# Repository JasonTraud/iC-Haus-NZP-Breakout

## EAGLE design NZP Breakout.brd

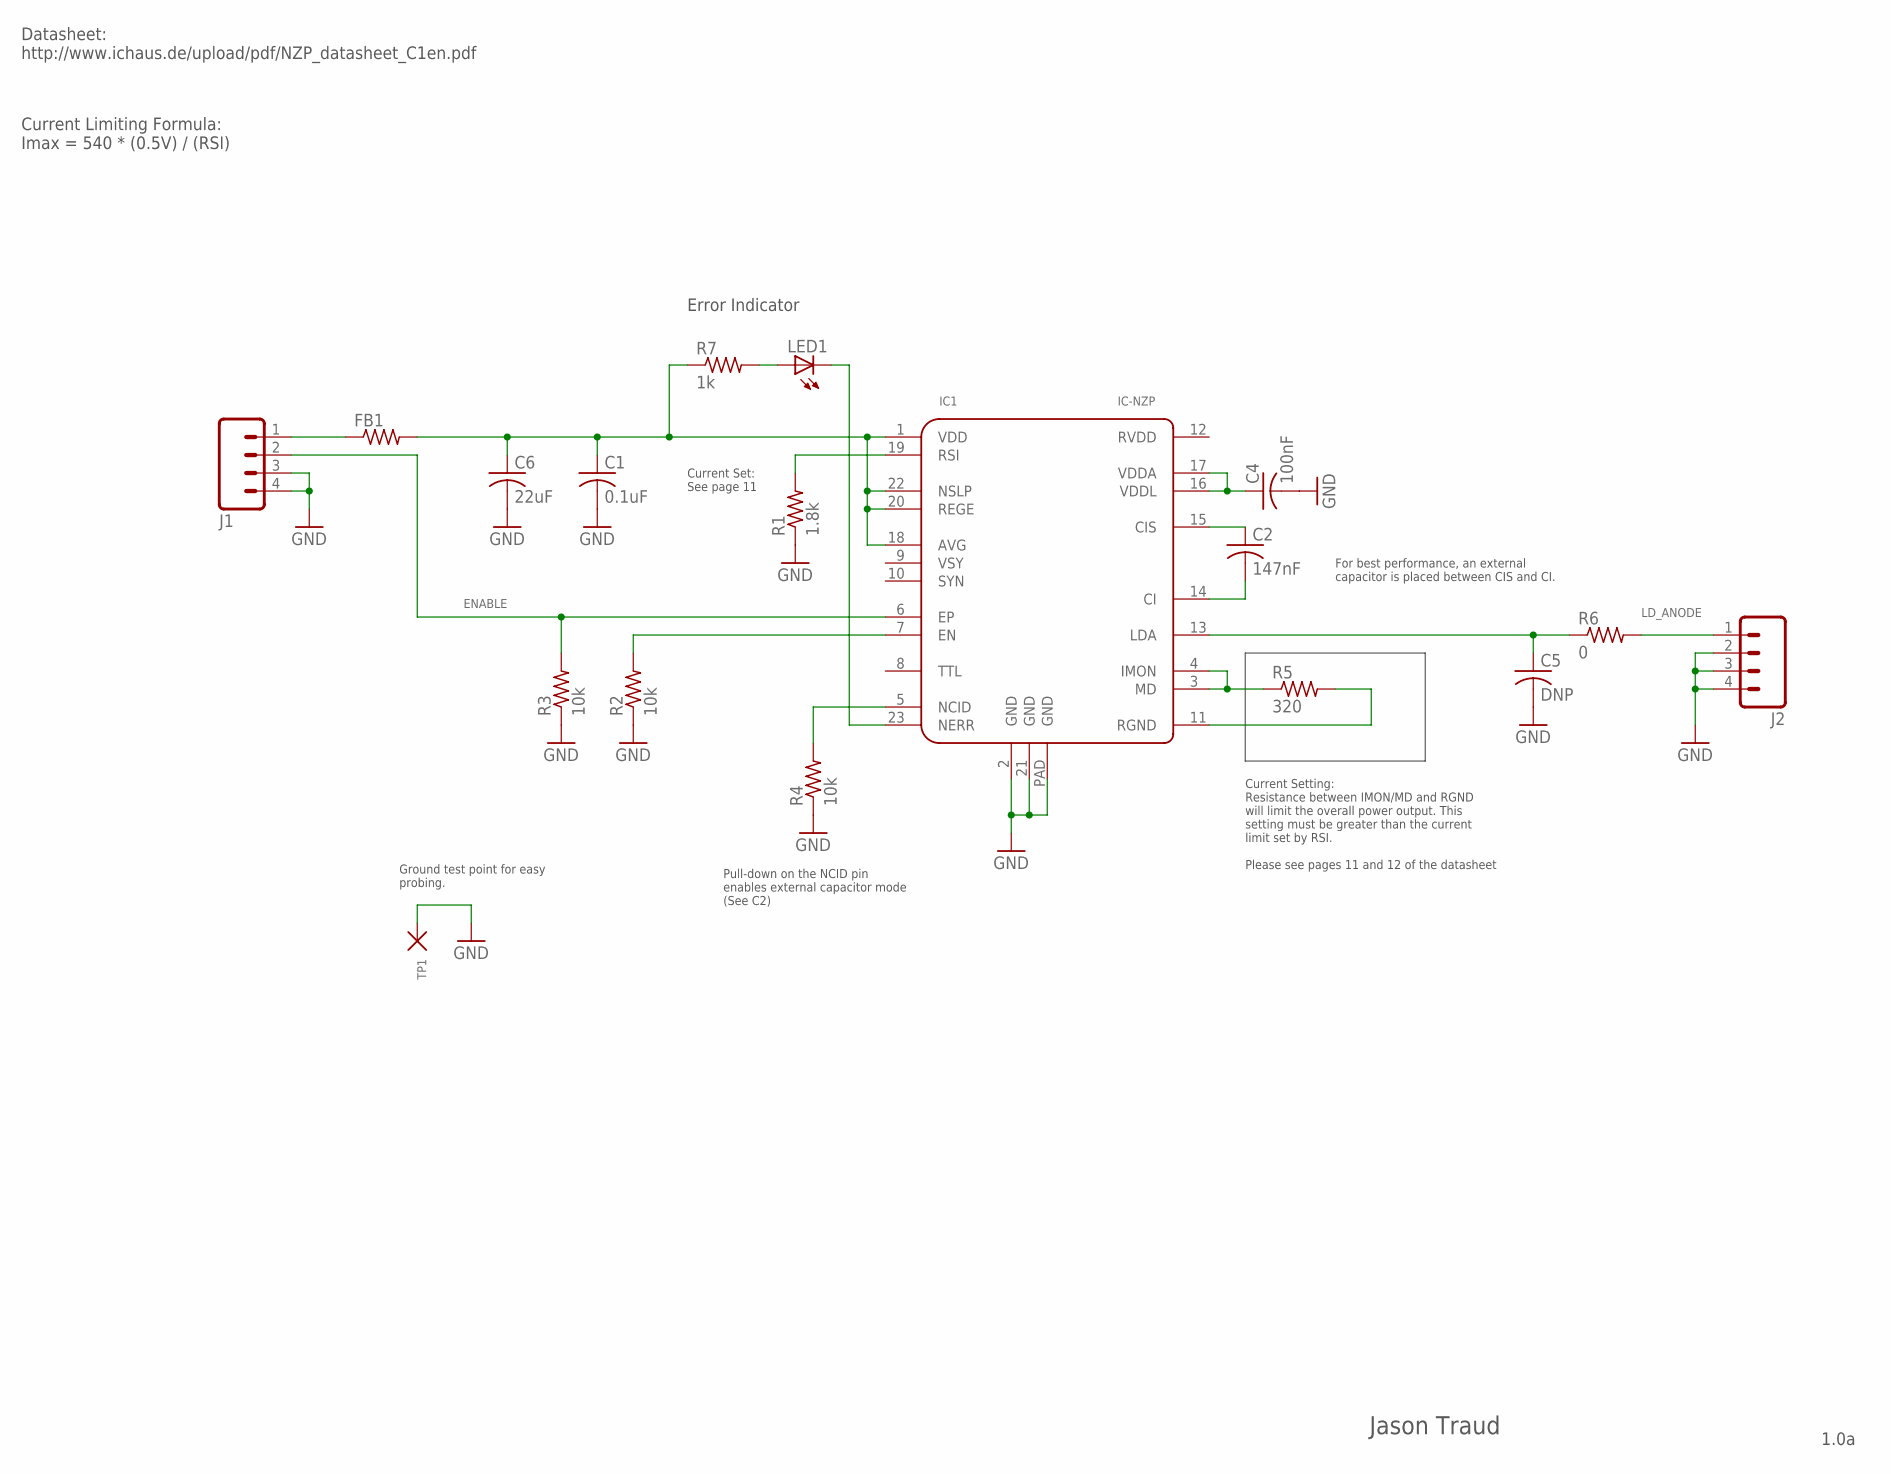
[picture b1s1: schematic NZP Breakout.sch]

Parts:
C1: 0.1uF; C0402
C2: 147nF; C0402
C4: 100nF; C0402
C5: DNP; C0805
C6: 22uF; C1206; MFG_PN TCTAL1C226M8R
FB1: R-US_R0805; R0805; MFG_PN MPZ2012S300A
IC1: IC-NZP; QFN24_PAD
J1, J2: 2X2; 2X2_1.27MM
LED1: LEDSML0805; SML0805
R1: 1.8k; R0402
R2, R3, R4: 10k; R0402
R5: 320; R0402
R6: 0; R0805
R7: 1k; R0402
TP1: TP

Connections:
ENABLE: IC1.6 (EP), J1.2, R3.2
GND: C1.2, C4.2, C5.2, C6.2, IC1.2 (GND), IC1.21 (GND), IC1.PAD (GND), J1.3, J1.4, J2.2, J2.3, J2.4, R1.1, R2.1, R3.1, R4.1, TP1.P$1
LD_ANODE: J2.1, R6.2
unnamed: IC1.5 (NCID), R4.2
unnamed: IC1.19 (RSI), R1.2
unnamed: IC1.23 (NERR), LED1.C
unnamed: C2.1, IC1.15 (CIS)
unnamed: C2.2, IC1.14 (CI)
unnamed: C4.1, IC1.16 (VDDL), IC1.17 (VDDA)
unnamed: FB1.1, J1.1
unnamed: IC1.3 (MD), IC1.4 (IMON), R5.1
unnamed: IC1.11 (RGND), R5.2
unnamed: C5.1, IC1.13 (LDA), R6.1
unnamed: LED1.A, R7.2
N_ENABLE: IC1.7 (EN), R2.2
VIN: C1.1, C6.1, FB1.2, IC1.1 (VDD), IC1.18 (AVG), IC1.20 (REGE), IC1.22 (NSLP), R7.1

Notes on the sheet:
Error Indicator
Current Setting: Resistance between IMON/MD and RGND will limit the overall power output. This setting must be greater than the current limit set by RSI. Please see pages 11 and 12 of the datasheet
For best performance, an external capacitor is placed between CIS and CI.
Pull-down on the NCID pin enables external capacitor mode (See C2)
Current Set: See page 11
Ground test point for easy probing.
Datasheet: http://www.ichaus.de/upload/pdf/NZP_datasheet_C1en.pdf
Current Limiting Formula: Imax = 540 * (0.5V) / (RSI)
Jason Traud
1.0a

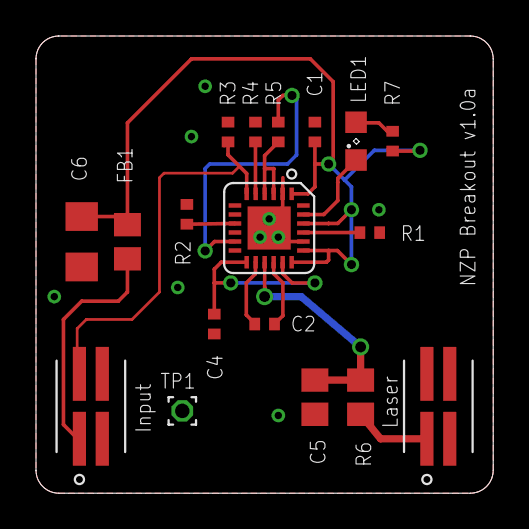
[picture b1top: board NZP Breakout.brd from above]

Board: 2 copper layers, 25.4 x 25.4 mm, 18 parts (0 on the bottom side), 16 nets.

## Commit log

2016-04-17 Initial Commit
    Initial Commit of design and documentation

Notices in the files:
parts and their libraries:
SparkFun-Aesthetics: Licensing: Creative Commons ShareAlike 4.0 International - https://creativecommons.org/licenses/by-sa/4.0
frames: Released under the Creative Commons
Attribution Share-Alike 4.0 License
https://creativecommons.org/licenses/by-sa/4.0
